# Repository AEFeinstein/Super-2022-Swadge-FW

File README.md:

# Super Magfest 2022 Swadge Firmware

## Welcome

This is the firmware repository for the Super Magfest 2022 Swadge.

The corresponding hardware repository for the Super Magfest 2022 Swadge [can be found here](https://github.com/AEFeinstein/Super-2021-Swadge-HW).

If you have any questions, feel free to create a Github ticket or email us at circuitboards@magfest.org.

## Continuous Integration

## History 

The Super Magfest 2022 Swadge is based on the [Super Magfest 2020 Swadge](https://github.com/AEFeinstein/Super-2020-Swadge-FW) and its [hardware repository](https://github.com/AEFeinstein/Super-2020-Swadge-HW).

The Super Magfest 2020 Swadge is based on the [2019 Swadge](https://github.com/cnlohr/swadge2019). The 2019 Swadge has a combined firmware and hardware repository.

The 2019 Swadge is based on [ESP8266 Colorchord](https://github.com/cnlohr/colorchord/tree/master/embedded8266). You can read more about [ColorChord: Embedded here](https://github.com/AEFeinstein/Swadge-Devkit-Fw/blob/master/firmware/embeddedcommon/README.md).

ESP8266 Colorchord uses [esp8266ws2812i2s](https://github.com/cnlohr/esp8266ws2812i2s), and is based on [ESP8266 MP3 Decoder](https://github.com/espressif/esp8266_mp3_decoder/).

## Working on this Project

If you would like to work on this project, start by following the [Getting Started Guide](/docs/GETTING_STARTED.md). By the end of the guide you should have an enviroment where you can compile the firmware and flash it to a Swadge.

There is also a [quick start script](/docs/swadge-setup.sh) which sets up a Linux environment (toolchain, dependencies, environment variables, and all) and builds the firmware.

Once your environment is set up, read the [Contribution Guide](/docs/CONTRIBUTING.md). This guide outlines the best practices for getting your code into this project.

There are a few more guides on [how to add modes to the Swadge](/docs/ADDING_MODES.md), [how to save persistent data](/docs/SAVING_DATA.md), and [how to connect Swadges wirelessly](/docs/P2P_CONNECTION.md).

The Super Magfest 2022 Swadge uses [cnlohr's exp8266 environment](https://github.com/cnlohr/esp82xx), which in turn uses the ESP8266 Non-OS SDK. You may find the [ESP8266 Non-OS SDK API Reference](https://www.espressif.com/sites/default/files/documentation/2c-esp8266_non_os_sdk_api_reference_en.pdf) useful.

[pyFlashGui](/pyFlashGui) is used for flashing Swadges. It's a Python GUI program.

[ESP Asset Packet](https://github.com/AEFeinstein/ESP-Asset-Packer) is used to process assets like png or gif files into a binary format which the Swadge firmware can use.

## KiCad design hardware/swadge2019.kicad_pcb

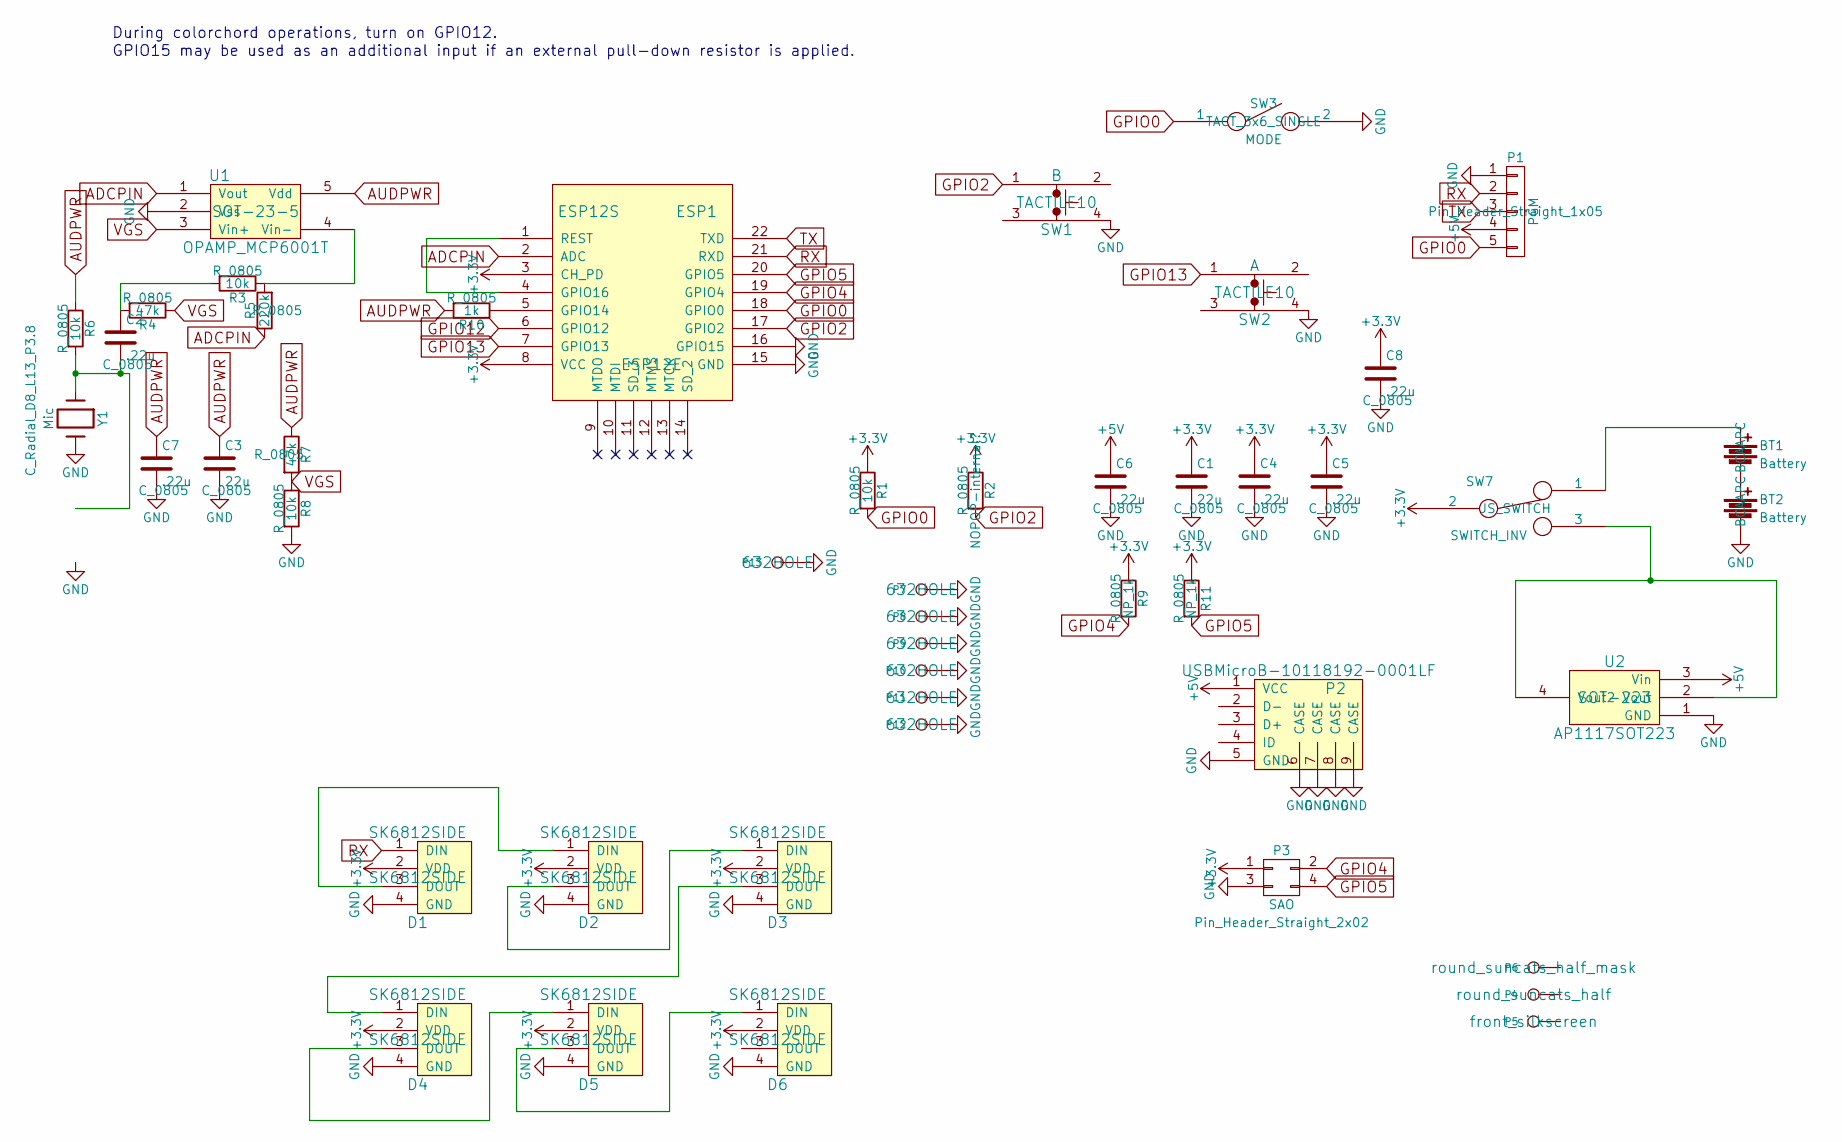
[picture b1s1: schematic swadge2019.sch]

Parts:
BT1, BT2: Battery; BCAAPC
C1, C3: 22u; C_0805
C2, C4, C5, C6, C7, C8: .22u; C_0805
D1, D2, D3, D4, D5, D6: SK6812SIDE
ESP1: ESP12S; ESP12E
P1: PGM; Pin_Header_Straight_1x05
P2: USBMicroB-10118192-0001LF
P3: SAO; Pin_Header_Straight_2x02
P4: CONN_1; round_suncats_half
P5: front_silkscreen
P6: CONN_1; round_suncats_half_mask
P7, P8, P9, P10, P11, P12, P13: CONN_1; 632HOLE
R1, R3, R6, R8: 10k; R_0805
R2: NOPOP-internal?; R_0805
R4, R7: 47k; R_0805
R5: 220k; R_0805
R9, R11: NP_1k; R_0805
R10: 1k; R_0805
SW1: B; TACTILE10
SW2: A; TACTILE10
SW3: MODE; TACT_3x6_SINGLE
SW7: SWITCH_INV; JS_SWITCH
U1: OPAMP_MCP6001T; SOT-23-5
U2: AP1117SOT223; SOT-223
Y1: Mic; C_Radial_D8_L13_P3.8

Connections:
+3V3: C1.1, C4.1, C5.1, C8.1, D1.2 (VDD), D2.2 (VDD), D3.2 (VDD), D4.2 (VDD), D5.2 (VDD), D6.2 (VDD), ESP1.3 (CH_PD), ESP1.8 (VCC), P3.1, R1.1, R2.1, R9.1, R11.1, SW7.2
+5V: C6.1, P1.4, P2.1 (VCC), U2.3 (Vin)
ADCPIN: ESP1.2 (ADC), R5.1, U1.1 (Vout)
AUDPWR: C3.1, C7.1, R6.1, R7.1, R10.2, U1.5 (Vdd)
GND: BT2.2, C1.2, C3.2, C4.2, C5.2, C6.2, C7.2, C8.2, D1.4 (GND), D2.4 (GND), D3.4 (GND), D4.4 (GND), D5.4 (GND), D6.4 (GND), ESP1.15 (GND), ESP1.16 (GPIO15), P1.1, P2.5 (GND), P2.6 (CASE), P2.7 (CASE), P2.8 (CASE), P2.9 (CASE), P3.3, P7.1, P8.1, P9.1, P10.1, P11.1, P12.1, P13.1, R8.2, SW1.4, SW2.4, SW3.2, U1.2 (Vss), U2.1 (GND), Y1.2
GPIO0: ESP1.18 (GPIO0), P1.5, R1.2, SW3.1
GPIO2: ESP1.17 (GPIO2), R2.2, SW1.1
GPIO4: ESP1.19 (GPIO4), P3.2, R9.2
GPIO5: ESP1.20 (GPIO5), P3.4, R11.2
GPIO13: ESP1.7 (GPIO13), SW2.1
unnamed: BT1.1, SW7.1
unnamed: BT1.2, BT2.1
unnamed: C2.1, R3.2, R4.2
unnamed: C2.2, R6.2, Y1.1
unnamed: D1.3 (DOUT), D2.1 (DIN)
unnamed: D2.3 (DOUT), D3.1 (DIN)
unnamed: D3.3 (DOUT), D4.1 (DIN)
unnamed: D4.3 (DOUT), D5.1 (DIN)
unnamed: D5.3 (DOUT), D6.1 (DIN)
unnamed: ESP1.1 (REST), ESP1.4 (GPIO16)
unnamed: ESP1.5 (GPIO14), R10.1
unnamed: R3.1, R5.2, U1.4 (Vin-)
unnamed: SW7.3, U2.2 (Vout), U2.4 (Vout2)
RX: D1.1 (DIN), ESP1.21 (RXD), P1.2
TX: ESP1.22 (TXD), P1.3
VGS: R4.1, R7.2, R8.1, U1.3 (Vin+)

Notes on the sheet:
During colorchord operations, turn on GPIO12.
GPIO15 may be used as an additional input if an external pull-down resistor is applied.

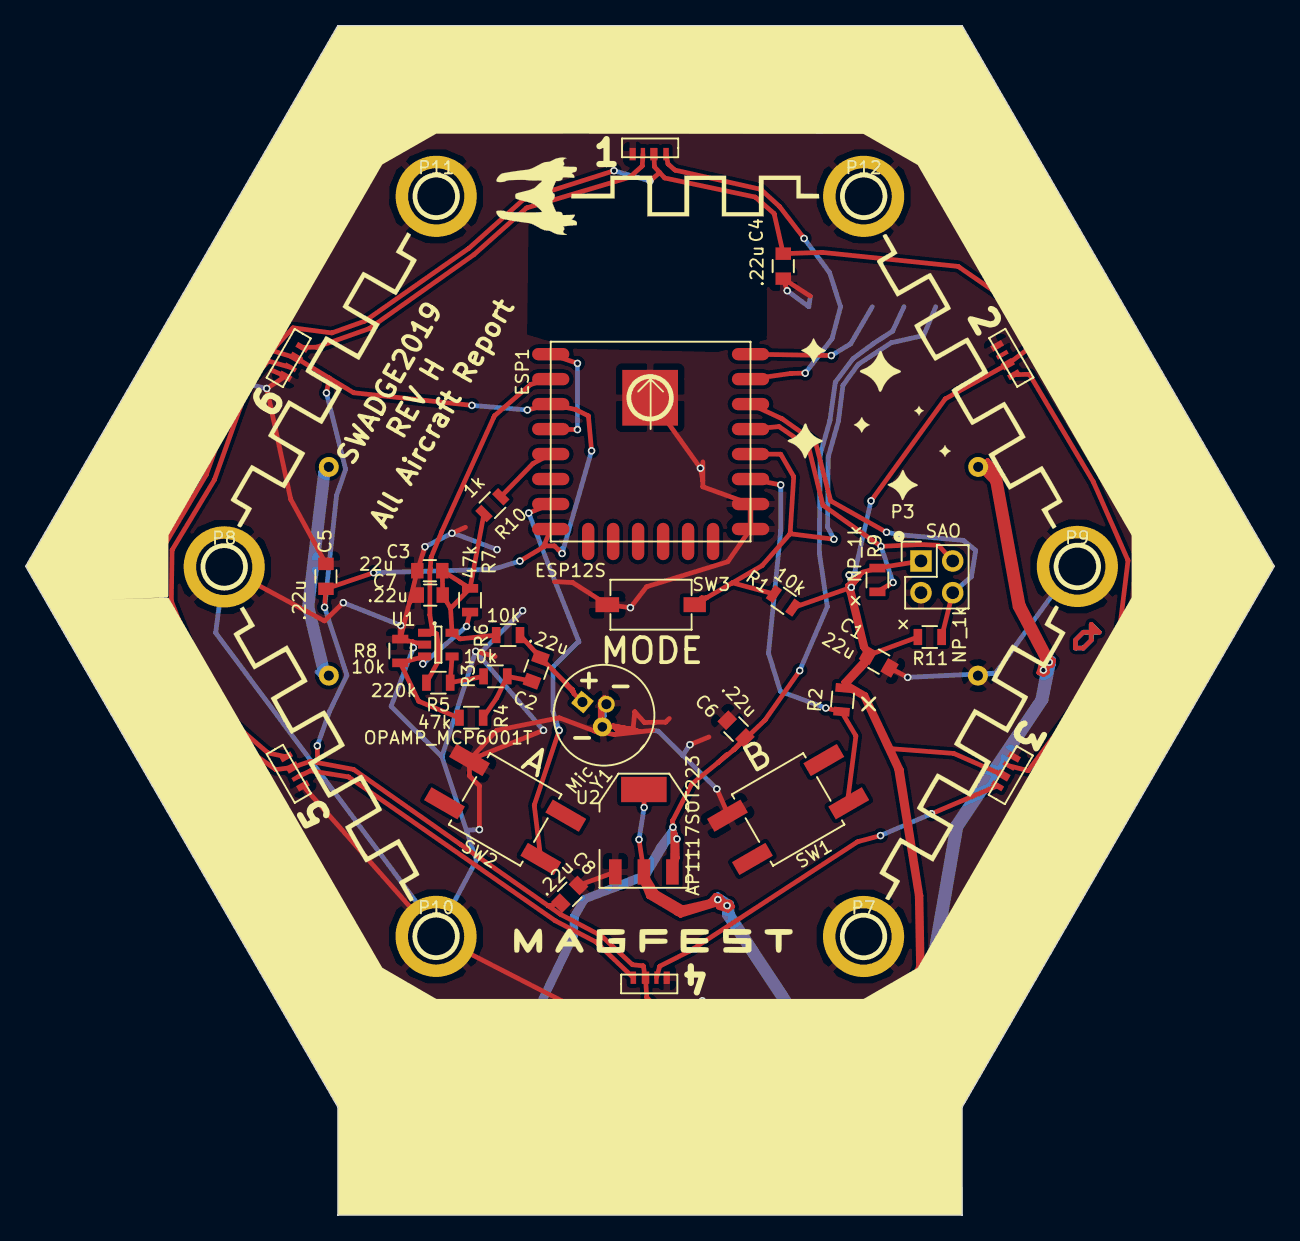
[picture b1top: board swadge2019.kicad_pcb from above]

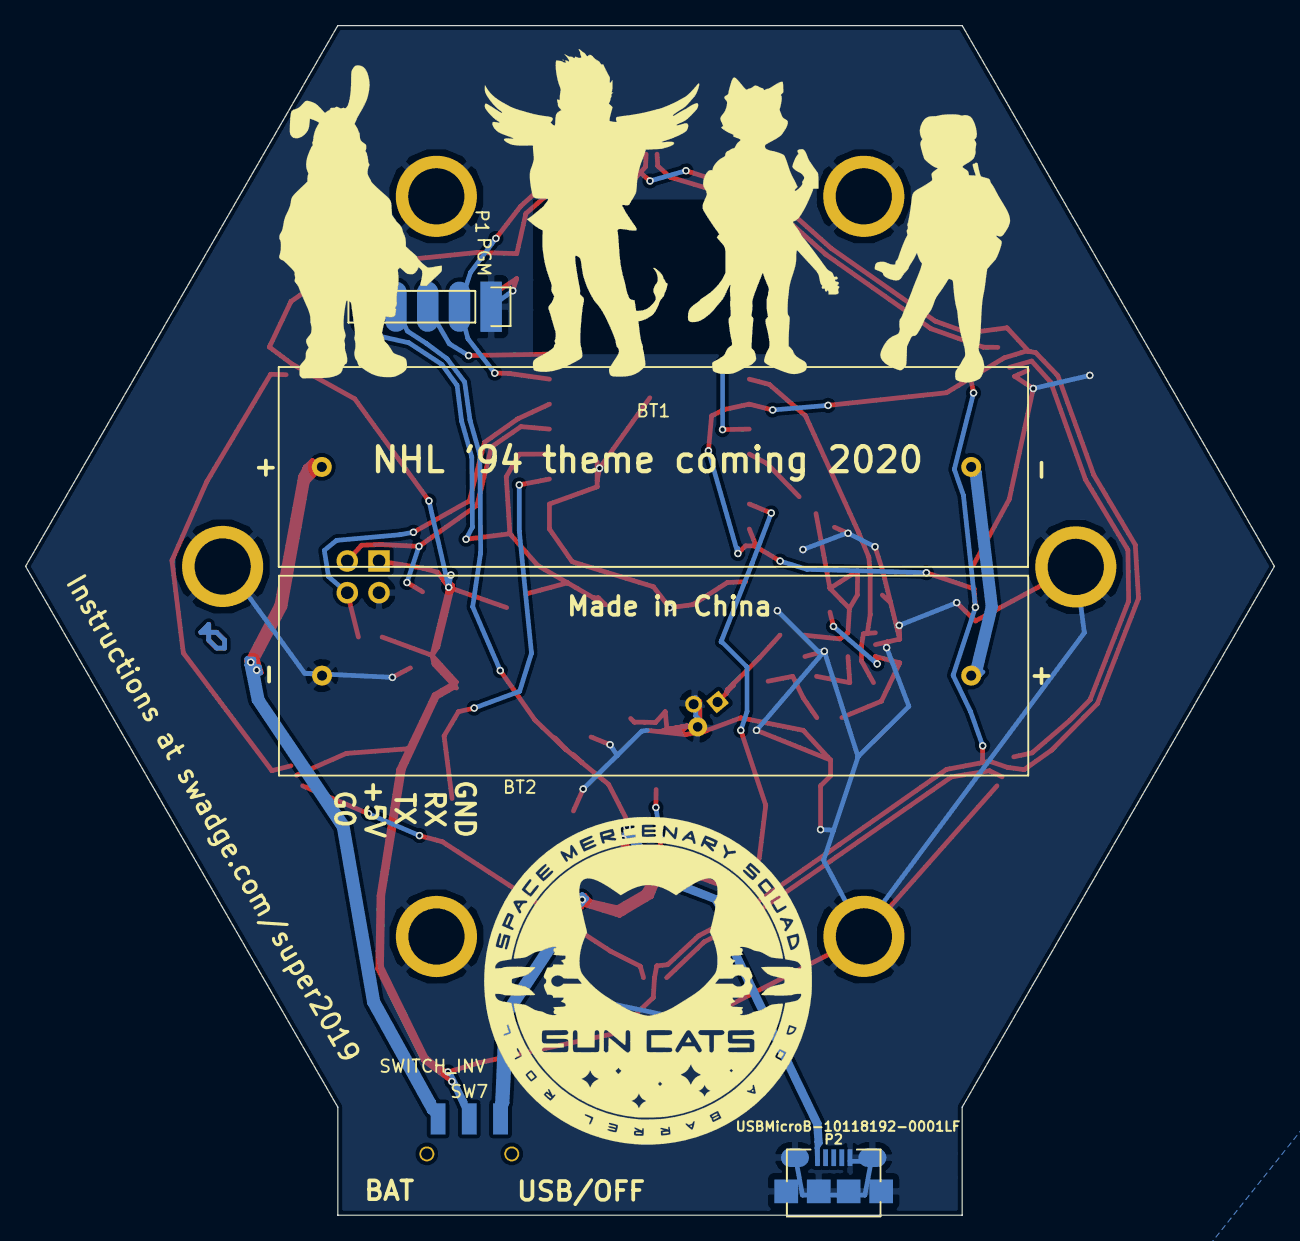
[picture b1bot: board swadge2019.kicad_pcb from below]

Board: 2 copper layers, 100.0 x 95.3 mm, 46 parts (5 on the bottom side), 26 nets.

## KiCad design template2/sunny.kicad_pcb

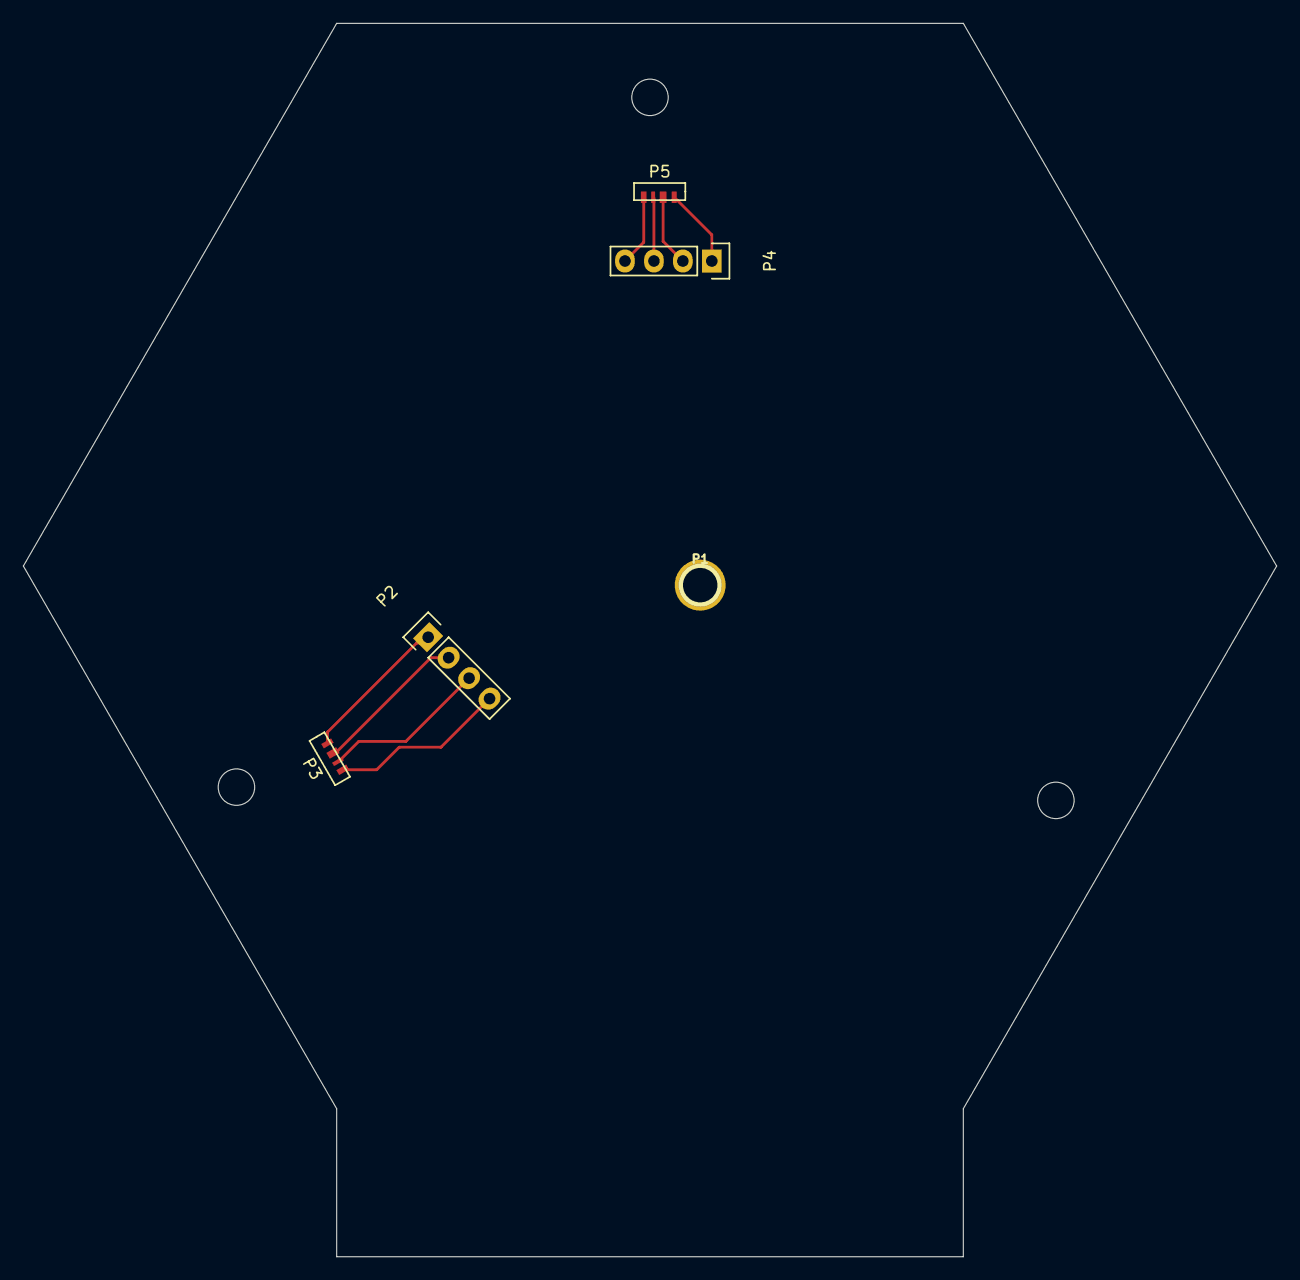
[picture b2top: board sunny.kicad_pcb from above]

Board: 2 copper layers, 110.0 x 108.3 mm, 5 parts (0 on the bottom side), 8 nets.

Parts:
P1: CONN_01X01; 632HOLE
P2, P4: CONN_01X04; Pin_Header_Straight_1x04
P3, P5: CONN_01X04; SK6812SIDE

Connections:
unnamed: P2.1, P3.1
unnamed: P2.2, P3.2
unnamed: P2.3, P3.3
unnamed: P2.4, P3.4
unnamed: P4.1, P5.1
unnamed: P4.2, P5.2
unnamed: P4.3, P5.3
unnamed: P4.4, P5.4

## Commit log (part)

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2020-09-26 #29 Allocate and free raycaster memory Move tan1024 to RODATA
2020-09-26 #29 fix textures draw at screen edge, efficiency
2020-09-26 Moved drawing functions from oled.c(s) to cndraw.c
    Fix warnings
2020-09-28 #20 Switch Demon to fnRenderTask
    Fix various animation glitches
2020-09-28 #20 speed up playing animation
2020-09-28 Add flight sim ish sorta thing.
2020-09-29 Fix inverted sprite plotting
2020-09-30 makes ddr scoreboard use keys for scrolling, removes leading zeros, addl cleanup
2020-09-30 Makefile now inject git hash to the build Git hash is checked on boot to run self test Self test not performed yet
2020-09-30 Fix CircleCI, maybe
2020-10-01 astyle
2020-10-02 Don't CI this branch
2020-10-03 #29 Added states for enemy sprites Sprites now zig and zag
2020-10-04 Added temporary raycaster assets
2020-10-04 #29 added walking animations by swapping textures
2020-10-04 Switch to gelakinetic's new timing system
2020-10-04 Update temp assets
2020-10-05 Change metronome bpm faster when button is held
2020-10-05 Added font source
2020-10-05 Add RSSI mode.
2020-10-05 Don't require a self test every new githash
2020-10-06 #29 Added HUD, shooting, and animation
2020-10-06 #29 draw musical note to HUD
2020-10-07 #29 Added enemy and player health tracking Flash an outline when getting shot Separated getting shot and dead enemy states
2020-10-08 #29 Added six-frame walking imp
2020-10-12 DDR mode changes: difficulty bugfixes, double reduction, adds health penalty for misfiring
2020-10-13 Refactored mode name, nulled unused callbacks for better perf, fixed button masks to work with other modes.
2020-10-15 #29 Made world map bigger Used https://www.dcode.fr/binary-image to convert image Print memory stats
2020-10-16 #29 Added project to convert PNGs to FPS map
2020-10-16 #29 Add another room Place enemies at spawn points
2020-10-17 #29 Reduce imp to a two frame mirrored walk Imp no longer stutters when picking a direction Added third wall texture
2020-10-17 Fixes to run GDB
2020-10-17 Fix compilation
2020-10-17 Emulator now fills malloc with garbage Fix raycaster warning Add more paths for vscode
2020-10-17 #29 Display enemies remaining count Exit to menu when all enemies are dead Fix bug which turned menu LEDs on
2020-10-18 UI for Tuner
2020-10-19 Make char* args in font.c/h consts
2020-10-19 Add arrow graphic
2020-10-19 Display notes names of strings for guitar and ukelele
2020-10-20 #29 Add saving and loading FPS scores Add high score display Initialize more in raycasterInitGame() Move spriteOrder[] and spriteDistance[] to local mem Draw correct time on round over screen
2020-10-20 Don't require self test for emulator
2020-10-20 Fix warning without braking metronome Don't require self test for the emulator Hide plotChar() and charWidth() from the world
2020-10-20 Lower FPS in tuner, correct vertical ukelele note centering
2020-10-20 Deduplicate tuner code, prep for more instruments
2020-10-20 Add violin mode to tuner
2020-10-21 Keep BPM and pause state when changing between tuner/metronome
2020-10-22 #29 Pretty up raycasterDrawRoundOver
2020-10-22 #29 Tidy up high scores
2020-10-22 #29 Rework drawOutlines to draw solid lines
2020-10-22 Fix a warning
2020-10-26 Prefix system functions
2020-10-26 #66 Add dummy values for RSSI mode emulation
2020-10-26 Fix bug which wouldn't draw certain chars
2020-10-26 Fix special char positions
2020-10-26 Update ESP-Asset-Packer reference
2020-10-26 Fix ESP-Asset-Packer reference
2020-10-26 Fix windows build (silly conflicts)
2020-10-27 Draw rectanguar spacebar
2020-10-27 Fix capital underlines
2020-10-27 Konami
2020-10-28 #65 Up and Down cycle menu LED patterns
2020-10-28 Add cppcheck makefile target Fix cppcheck issues
2020-10-30 #29 Corpses no longer block shots
2020-10-30 #29 Refactored animation frames Easier to support multiple frames now
2020-11-04 #29 Blink icons in sync with LEDs
2020-11-08 Added Hateth Note
2020-11-09 update with flashing sphere
2020-11-10 Update mode, with lights animations. It feels like a game now.
2020-11-10 Oops - forgot to fixup two walls
2020-11-10 TABS TO SPACES
2020-11-10 Some QoL adjustments and make end screen not just exit.
2020-11-10 Adjust speeds, adding min flight speed.
2020-11-11 Initial attempt at tuner pendulum
2020-11-13 LED radar points to nearest sprite
2020-11-13 Make enemies faster on harder difficulties Scale health with difficulty
2020-11-14 Fix up personal demon LEDs
2020-11-14 Renamed raycaster to Shredder
2020-11-14 Replace colorchord LED UI with OLED UI
2020-11-14 Fix top level menu button behavior
2020-11-15 Fix random warnings
2020-11-18 Added different enemy types, skeleton of enemy wave behavior, and change projectile struct for more precise movement directions.
2020-11-18 Fix needle behavior Align text better, draw flat symbol Make LED behavior smoother
2020-11-18 Redraw menu icons Fixed bug where arrows wouldn't draw after screensaver
2020-11-18 First playable, fixed enemy wave spawning behavior issues, fixed immortal enemy bug, tweaked behavior or reflect power in response to playtesting.
2020-11-27 Update rawdraw to a stable tag
2020-12-02 Make pure random smoother
2020-12-03 Made random a little more random
2020-12-06 Update flight menu Mkae fire a little more firey
2020-12-06 Add status icons to personal demon Add text when refusing to play Move cake closer to demon Don't enqueue EVT_LOST_DISCIPLINE for kids
2020-12-07 Update code for a more mature flight experience. Measuring time in seconds, 100% etc.
2020-12-07 Change languge to 'unruly' Add randomness to ball playing animation
2020-12-07 Math is rad
2020-12-08 Add instructions for saving data to NVM
2020-12-08 Remove unnecessary prototypes Fix warnings
2020-12-08 Comment out unused drawing and compressing code
2020-12-09 Added LED dance names
2020-12-09 Added personal demon cat sprite
2020-12-09 Rework personal demon sprites
2020-12-09 #ifdef bresenham funcs Remove fastlz compressor
2020-12-09 Don't plot high score title in loop
2020-12-10 Bound the flight area
2020-12-10 Added hold-to-quit to tunernome emulator segfaults when starting menu timers after quitting tunernome
2020-12-10 Disabled more debugging
2020-12-11 Increase BPM even faster after 2s
2020-12-12 Remove fshort-enums compiler flag
    Use uint8_t type for worldMap instead of WorldMapTile_t to save space now that enums aren't short
2020-12-12 Properly initialize selftest memory
2020-12-12 Added time to the emulator
2020-12-12 Save last used SSID and PW to NVM
2020-12-13 Fix midnight time print
2020-12-15 Change radar color if the closest spr
2020-12-15 Briefly invert sprite colors after getting shot
2020-12-15 Adjust outlined heart in PersonalDemon
2020-12-15 Ignore buttons for 2s when showing GAME OVER
    Don't show inverted icons for GAME OVER
2020-12-15 Plot elapsed time for Shredder
    Monospace the numbers in fonts
2020-12-16 Started adding map select
2020-12-16 Rotate maps so that the top left is origin mapconv.c now processes multiple maps
2020-12-16 Tweak enemy health
    Don't draw timer on game over screen
2020-12-16 * Disable moving into other modes until connection complete. * Specify IP for PF on command line.
2020-12-17 cleanup testpixelflut
2020-12-17 Cleanup mode RSSI (astyle)
    Action button toggles RSSI LEDs, instead of a separate submode
    Move NTP & socket creation so it always happens
2020-12-17 Added smallest map
2020-12-17 Max out gain for Colorchord Start gain in the middle of the scale
2020-12-17 Print gain for tuner
2020-12-18 Plot currently listening note
    Also set colorchord-like LEDs
2020-12-19 Added wheel of fortune animation, no logic yet
2020-12-19 Position demon better for wheel of fortune
2020-12-19 Demon reacts to wheel outcome
2020-12-19 Code cleanup
2020-12-22 Add bird demon, save some code space
2020-12-22 outlined demons, but not the bat
2020-12-23 Collected #defines for raycaster
2020-12-23 Increase player move speed on hard by 20%
2020-12-23 Add invincibility frames, which flicker
    Remove the sprite flicker immediately after being shot
2020-12-23 Add double-tap strafe
2020-12-23 Strafing now dodges shots
    Shots now fired after whole shooting animation
2020-12-23 Outline guitar
2020-12-23 Disable debounce for Colorchord
2020-12-23 Increase max speed
2020-12-27 Delay one day between fat/thin and losing health
2020-12-27 Extract demon probabilities
    Make medicine 85% effective
2020-12-27 Scroll text faster when there's more in the queue
2020-12-27 Comments
2020-12-27 Fix menu item removeal (untested)
2020-12-27 Chalice is now an item
2020-12-31 Attempt to update slack integration
2021-01-01 Call pip3 differently
2021-01-01 Alias python3.8
2021-01-01 Install python3
    cygwin can't specify a version on the command line, so i hope it doesn't change again...
2021-01-01 Actually fix notifications
2021-01-05 Dumb fire stuff
2021-01-06 Added null dance
2021-01-06 Update comment
2021-01-07 moved screensavers
2021-01-07 Screensavers alloc & free RAM
    Remove MatrixFastFire
2021-01-09 Added MatrixRain screenaver
    Added WHITE_F_TRANSPARENT_B when drawing sprites
    Added shadeDisplayArea() to blot out areas
    Fixed bug in charWidth(), made public
2021-01-12 Safer screensaver init and destroy
2021-01-12 Added lives system, player starts with 3 lives, gameover when player dies with 0 lives. Powerups will now drift left off screen after a short delay. Removed debug display of enemy waves. Fixed bug wh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
2021-01-16 Fix menu button behavior
2021-02-10 Fix CI
2021-02-15 Added "Die For Me" difficulty, which greatly scales enemy numbers. Hard and "Die For Me" difficulty now ignore the first 3 tutorial waves. Difficulty now effects the chance of spawning powerups (Less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
2021-02-15 Asset integration for M-Type player, enemies, powerup, and explosions. Added function to draw PNG sequences that supports inverse behavior. Changed memory settings to resolve iram overflow issues. Ad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
2021-02-16 Free explosionSequenceHandle Use floats instead of double Have drawPngSequence() call drawPngSequenceInv()
2021-02-16 Added "MAP SELECT" text
2021-02-16 Slow down screensavers by 30%
2021-02-24 Attempt to fix CI, again
2021-02-24 Move artifact from cygwin to Windows dir
2021-02-24 Un-parallelize CI, fix slack notification
2021-02-24 Fix windows path
2021-02-25 Added lower bound for number of enemies in a formation.
    Added lower bound for the number of enemies that are spawned in a formation for different waves, currently set by difficulty (1 for easy, 2 for medium, etc.). Fixes bug with creation of enemy formati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
2021-04-30 Update slack orb
2021-06-10 Remove python2 dependency, use local esptool.py
2021-08-27 Update 'enemies left' icon for Shredder
2021-08-27 Consolidate common menu strings
2021-08-27 Added fast smooth rainbow
2021-08-27 Fix a typo
2021-08-27 Add vscode defines. They do not affect the build!
2021-08-28 Doom-ify difficulty strings
    Start difficulties on 'medium'
    Replace hard with v_hard for Shredder
2021-09-07 Filled gaps in maps, astyled raycaster
2021-09-27 improved collision support for porjectiles, improved spawning behavior, fixed bug with dead player collisions.
2021-09-29 Update screensaver year, version
2021-09-29 Added total NVM reset in easter egg Fixed crash when exiting easter egg
2021-09-29 Add githash to easter egg menu Clear LEDs when switching easter egg modes
2021-09-29 Added option to kill personal demon Allow memorials to have 0 days Default NVM memorials to -1 days
2021-09-29 Move FPS maps to ROM Unpack WorldMapTile_t for better ROM alignment
2021-09-30 Added Credits to Easter Egg
2021-09-30 Only show 'connect last' if SSID is saved
2021-09-30 #90 Stomp - Center top and bottom row sprites
2021-10-02 Fix empty screensaver LED animation names
2021-10-02 Update credits names
2021-10-02 Disable timerScreensaverStart when starting
2021-10-04 DDR: added feedback text for notes Vertically centered text better
2021-10-04 Rework DDR LEDs with calibrated offsets
2021-10-06 Flipped demon bird to face left
2021-10-06 Fixed esptool warning
2021-10-06 Credits now have fast scrolling up/down Credits resets to normal position when restarting
2021-10-07 Fix the last warning
2021-11-11 Add zlib dep for CI
2021-11-11 Removed Sandbox from repo name. Fixed mapconf clean
2021-11-13 Spell ukulele correctly Use 'quit' instead of 'exit'
2022-01-12 Added image
